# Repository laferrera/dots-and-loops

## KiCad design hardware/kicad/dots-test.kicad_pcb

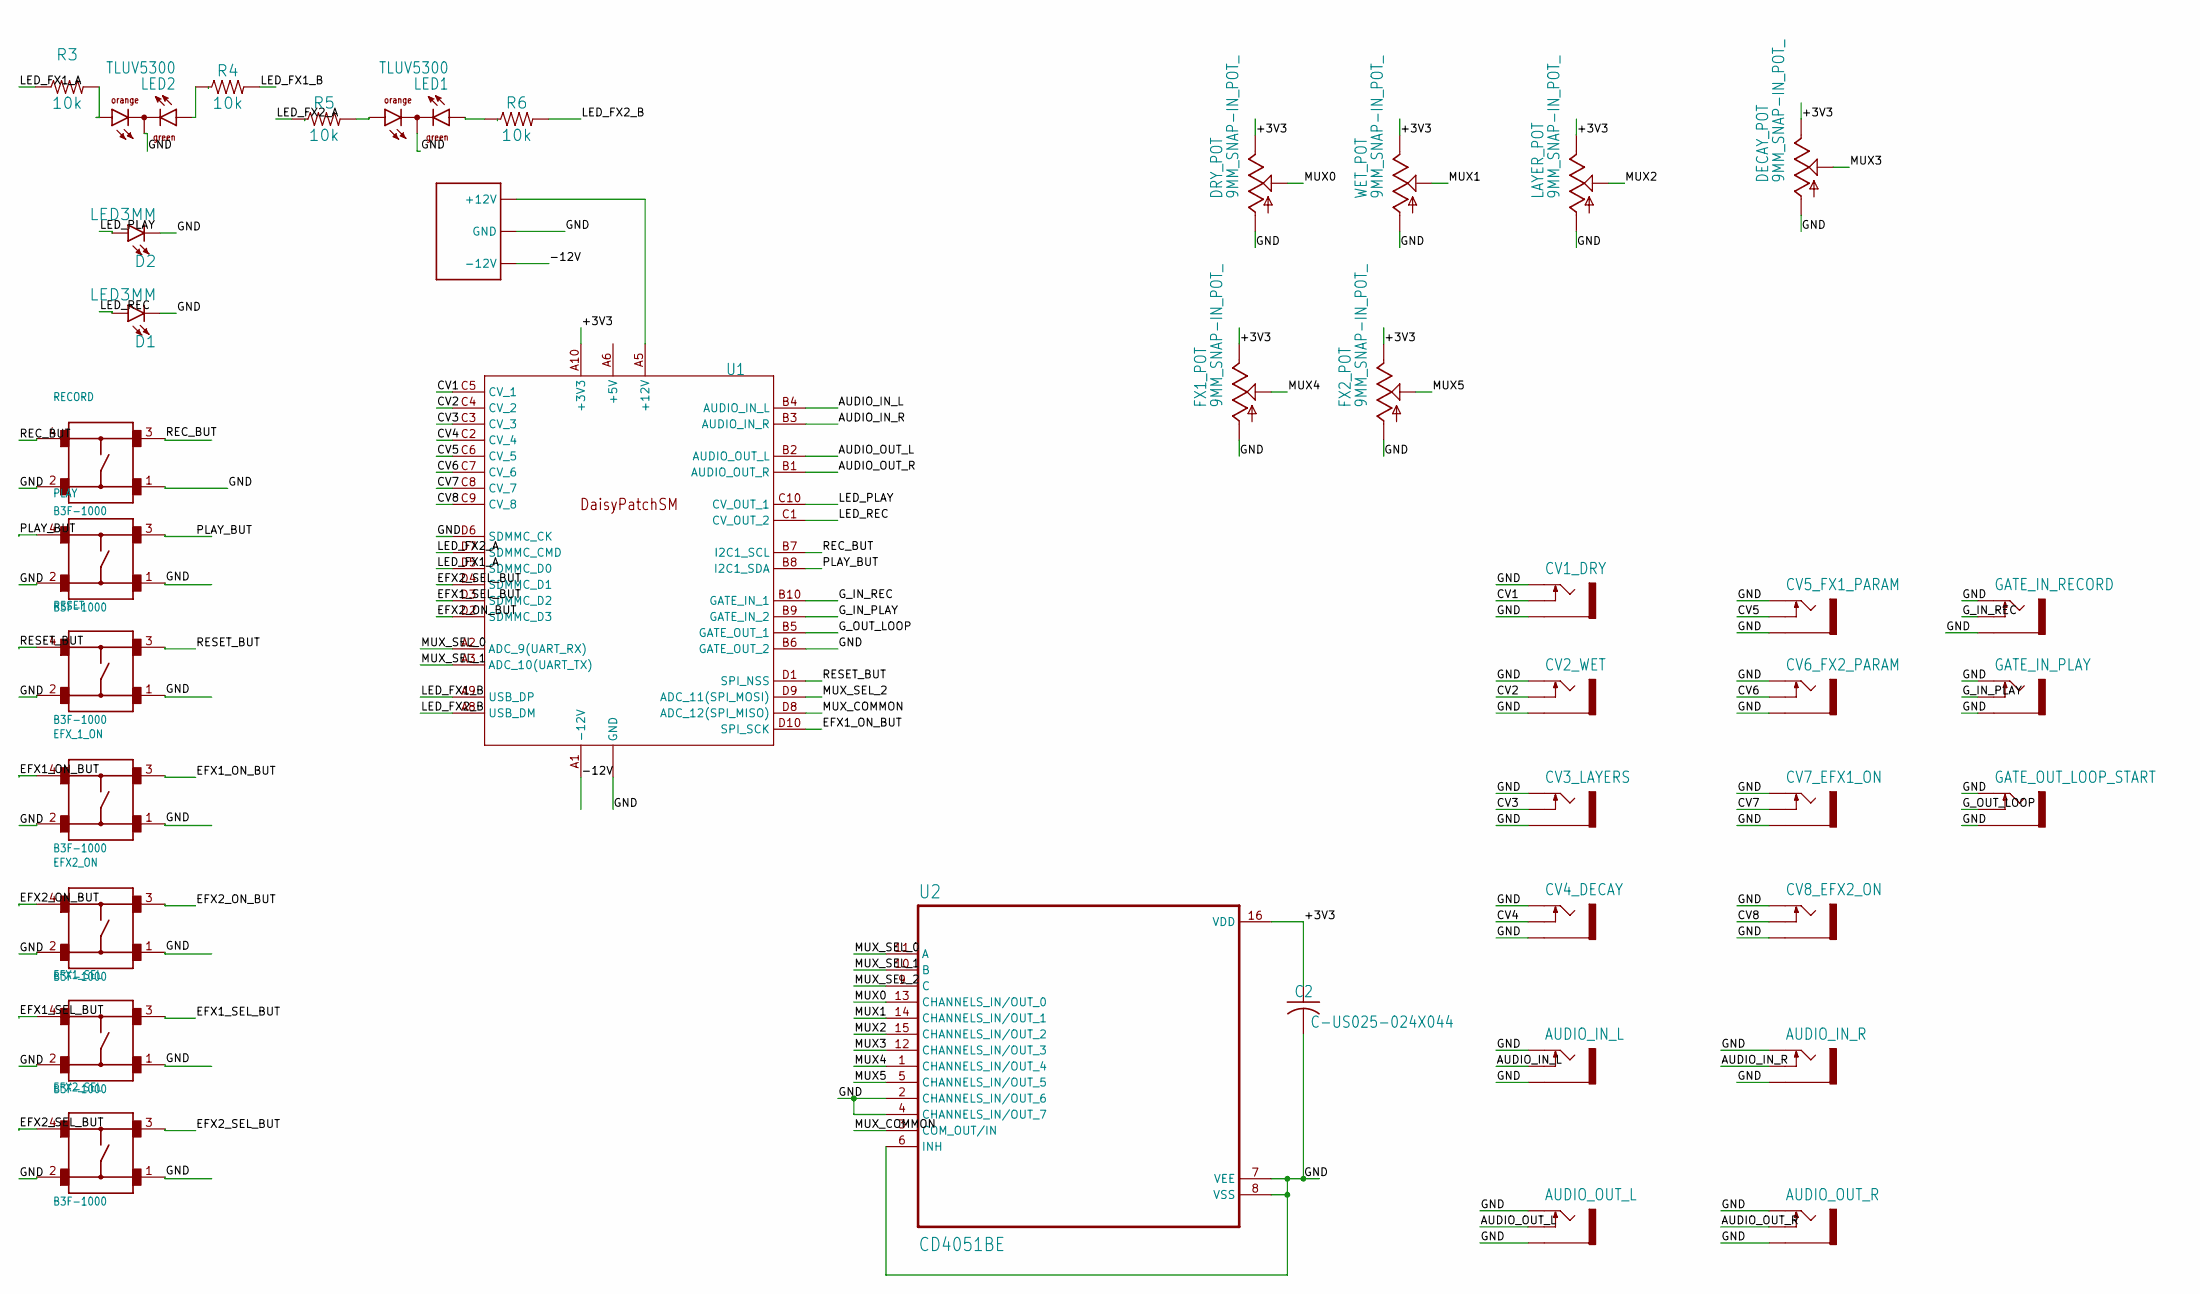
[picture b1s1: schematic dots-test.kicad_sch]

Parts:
AUDIO_IN_L: THONKICONNNEW; WQP-PJ301M-12_JACK
AUDIO_IN_R: THONKICONNNEW; WQP-PJ301M-12_JACK
AUDIO_OUT_L: THONKICONNNEW; WQP-PJ301M-12_JACK
AUDIO_OUT_R: THONKICONNNEW; WQP-PJ301M-12_JACK
C1: EURO_POWER_LOCKFAT-LOCK; EURO_PWR_HEADER_LOCK
C2: C-US025-024X044; C025-024X044
CV1_DRY, CV2_WET, CV3_LAYERS, CV4_DECAY, CV5_FX1_PARAM, CV6_FX2_PARAM, CV7_EFX1_ON, CV8_EFX2_ON: THONKICONNNEW; WQP-PJ301M-12_JACK
D1, D2: LED3MM; LED_3MM
DECAY_POT: 9MM_SNAP-IN_POT_; 9MM_SNAP-IN_POT
DRY_POT: 9MM_SNAP-IN_POT_; 9MM_SNAP-IN_POT
EFX1_SEL, EFX2_ON, EFX2_SEL: B3F-1000
EFX_1_ON: B3F-1000
FX1_POT, FX2_POT: 9MM_SNAP-IN_POT_; 9MM_SNAP-IN_POT
GATE_IN_PLAY: THONKICONNNEW; WQP-PJ301M-12_JACK
GATE_IN_RECORD: THONKICONNNEW; WQP-PJ301M-12_JACK
GATE_OUT_LOOP_START: THONKICONNNEW; WQP-PJ301M-12_JACK
LAYER_POT: 9MM_SNAP-IN_POT_; 9MM_SNAP-IN_POT
LED1, LED2: TLUV5300
PLAY: B3F-1000
R3, R4, R5, R6: 10k; AXIAL-0.3
RECORD: B3F-1000
RESET: B3F-1000
U1: ES_DAISY_PATCH_SMULTRA_LOCK; ES_DAISY_PATCH_SM_REV1_ULTRA_LOCK
U2: CD4051BE; DIP794W45P254L1969H508Q16
WET_POT: 9MM_SNAP-IN_POT_; 9MM_SNAP-IN_POT

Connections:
+3V3: C2.1, DECAY_POT.3 (E), DRY_POT.3 (E), FX1_POT.3 (E), FX2_POT.3 (E), LAYER_POT.3 (E), U1.A10 (+3V3), U2.16 (VDD), WET_POT.3 (E)
-12V: C1.NEG1 (-12V), C1.NEG2 (-12V), U1.A1 (-12V)
AUDIO_IN_L: AUDIO_IN_L.P$2_SWITCH (SWITCH), U1.B4 (AUDIO_IN_L)
AUDIO_IN_R: AUDIO_IN_R.P$2_SWITCH (SWITCH), U1.B3 (AUDIO_IN_R)
AUDIO_OUT_L: AUDIO_OUT_L.P$2_SWITCH (SWITCH), U1.B2 (AUDIO_OUT_L)
AUDIO_OUT_R: AUDIO_OUT_R.P$2_SWITCH (SWITCH), U1.B1 (AUDIO_OUT_R)
CV1: CV1_DRY.P$2_SWITCH (SWITCH), U1.C5 (CV_1)
CV2: CV2_WET.P$2_SWITCH (SWITCH), U1.C4 (CV_2)
CV3: CV3_LAYERS.P$2_SWITCH (SWITCH), U1.C3 (CV_3)
CV4: CV4_DECAY.P$2_SWITCH (SWITCH), U1.C2 (CV_4)
CV5: CV5_FX1_PARAM.P$2_SWITCH (SWITCH), U1.C6 (CV_5)
CV6: CV6_FX2_PARAM.P$2_SWITCH (SWITCH), U1.C7 (CV_6)
CV7: CV7_EFX1_ON.P$2_SWITCH (SWITCH), U1.C8 (CV_7)
CV8: CV8_EFX2_ON.P$2_SWITCH (SWITCH), U1.C9 (CV_8)
EFX1_ON_BUT: EFX_1_ON.3, EFX_1_ON.4, U1.D10 (SPI_SCK)
EFX1_SEL_BUT: EFX1_SEL.3, EFX1_SEL.4, U1.D3 (SDMMC_D2)
EFX2_ON_BUT: EFX2_ON.3, EFX2_ON.4, U1.D2 (SDMMC_D3)
EFX2_SEL_BUT: EFX2_SEL.3, EFX2_SEL.4, U1.D4 (SDMMC_D1)
GND: AUDIO_IN_L.P$1_TIP (TIP), AUDIO_IN_L.P$3_SLEEVE (SLEEVE), AUDIO_IN_R.P$1_TIP (TIP), AUDIO_IN_R.P$3_SLEEVE (SLEEVE), AUDIO_OUT_L.P$1_TIP (TIP), AUDIO_OUT_L.P$3_SLEEVE (SLEEVE), AUDIO_OUT_R.P$1_TIP (TIP), AUDIO_OUT_R.P$3_SLEEVE (SLEEVE), C1.GND1 (GND), C1.GND2 (GND), C1.GND3 (GND), C1.GND4 (GND), C1.GND5 (GND), C1.GND6 (GND), C2.2, CV1_DRY.P$1_TIP (TIP), CV1_DRY.P$3_SLEEVE (SLEEVE), CV2_WET.P$1_TIP (TIP), CV2_WET.P$3_SLEEVE (SLEEVE), CV3_LAYERS.P$1_TIP (TIP), CV3_LAYERS.P$3_SLEEVE (SLEEVE), CV4_DECAY.P$1_TIP (TIP), CV4_DECAY.P$3_SLEEVE (SLEEVE), CV5_FX1_PARAM.P$1_TIP (TIP), CV5_FX1_PARAM.P$3_SLEEVE (SLEEVE), CV6_FX2_PARAM.P$1_TIP (TIP), CV6_FX2_PARAM.P$3_SLEEVE (SLEEVE), CV7_EFX1_ON.P$1_TIP (TIP), CV7_EFX1_ON.P$3_SLEEVE (SLEEVE), CV8_EFX2_ON.P$1_TIP (TIP), CV8_EFX2_ON.P$3_SLEEVE (SLEEVE), D1.K (C), D2.K (C), DECAY_POT.1 (A), DRY_POT.1 (A), EFX1_SEL.1, EFX1_SEL.2, EFX2_ON.1, EFX2_ON.2, EFX2_SEL.1, EFX2_SEL.2, EFX_1_ON.1, EFX_1_ON.2, FX1_POT.1 (A), FX2_POT.1 (A), GATE_IN_PLAY.P$1_TIP (TIP), GATE_IN_PLAY.P$3_SLEEVE (SLEEVE), GATE_IN_RECORD.P$1_TIP (TIP), GATE_IN_RECORD.P$3_SLEEVE (SLEEVE), GATE_OUT_LOOP_START.P$1_TIP (TIP), GATE_OUT_LOOP_START.P$3_SLEEVE (SLEEVE), LAYER_POT.1 (A), LED1.CC, LED2.CC, PLAY.1, PLAY.2, RECORD.1, RECORD.2, RESET.1, RESET.2, U1.A4 (GND), U1.A7 (GND), U1.B6 (GATE_OUT_2), U1.D6 (SDMMC_CK), U2.2 (CHANNELS_IN/OUT_6), U2.4 (CHANNELS_IN/OUT_7), U2.6 (INH), U2.7 (VEE), U2.8 (VSS), WET_POT.1 (A)
G_IN_PLAY: GATE_IN_PLAY.P$2_SWITCH (SWITCH), U1.B9 (GATE_IN_2)
G_IN_REC: GATE_IN_RECORD.P$2_SWITCH (SWITCH), U1.B10 (GATE_IN_1)
G_OUT_LOOP: GATE_OUT_LOOP_START.P$2_SWITCH (SWITCH), U1.B5 (GATE_OUT_1)
LED_FX1_A: R3.P$1 (1), U1.D5 (SDMMC_D0)
LED_FX1_B: R4.P$2 (2), U1.A9 (USB_DP)
LED_FX2_A: R5.P$1 (1), U1.D7 (SDMMC_CMD)
LED_FX2_B: R6.P$2 (2), U1.A8 (USB_DM)
LED_PLAY: D2.A, U1.C10 (CV_OUT_1)
LED_REC: D1.A, U1.C1 (CV_OUT_2)
MUX0: DRY_POT.2 (S), U2.13 (CHANNELS_IN/OUT_0)
MUX1: U2.14 (CHANNELS_IN/OUT_1), WET_POT.2 (S)
MUX2: LAYER_POT.2 (S), U2.15 (CHANNELS_IN/OUT_2)
MUX3: DECAY_POT.2 (S), U2.12 (CHANNELS_IN/OUT_3)
MUX4: FX1_POT.2 (S), U2.1 (CHANNELS_IN/OUT_4)
MUX5: FX2_POT.2 (S), U2.5 (CHANNELS_IN/OUT_5)
MUX_COMMON: U1.D8 (ADC_12(SPI_MISO)), U2.3 (COM_OUT/IN)
MUX_SEL_0: U1.A2 (ADC_9(UART_RX)), U2.11 (A)
MUX_SEL_1: U1.A3 (ADC_10(UART_TX)), U2.10 (B)
MUX_SEL_2: U1.D9 (ADC_11(SPI_MOSI)), U2.9 (C)
unnamed: C1.POS1 (+12V), C1.POS2 (+12V), U1.A5 (+12V)
unnamed: LED2.AO, R3.P$2 (2)
unnamed: LED2.AG, R4.P$1 (1)
unnamed: LED1.AO, R5.P$2 (2)
unnamed: LED1.AG, R6.P$1 (1)
PLAY_BUT: PLAY.3, PLAY.4, U1.B8 (I2C1_SDA)
REC_BUT: RECORD.3, RECORD.4, U1.B7 (I2C1_SCL)
RESET_BUT: RESET.3, RESET.4, U1.D1 (SPI_NSS)

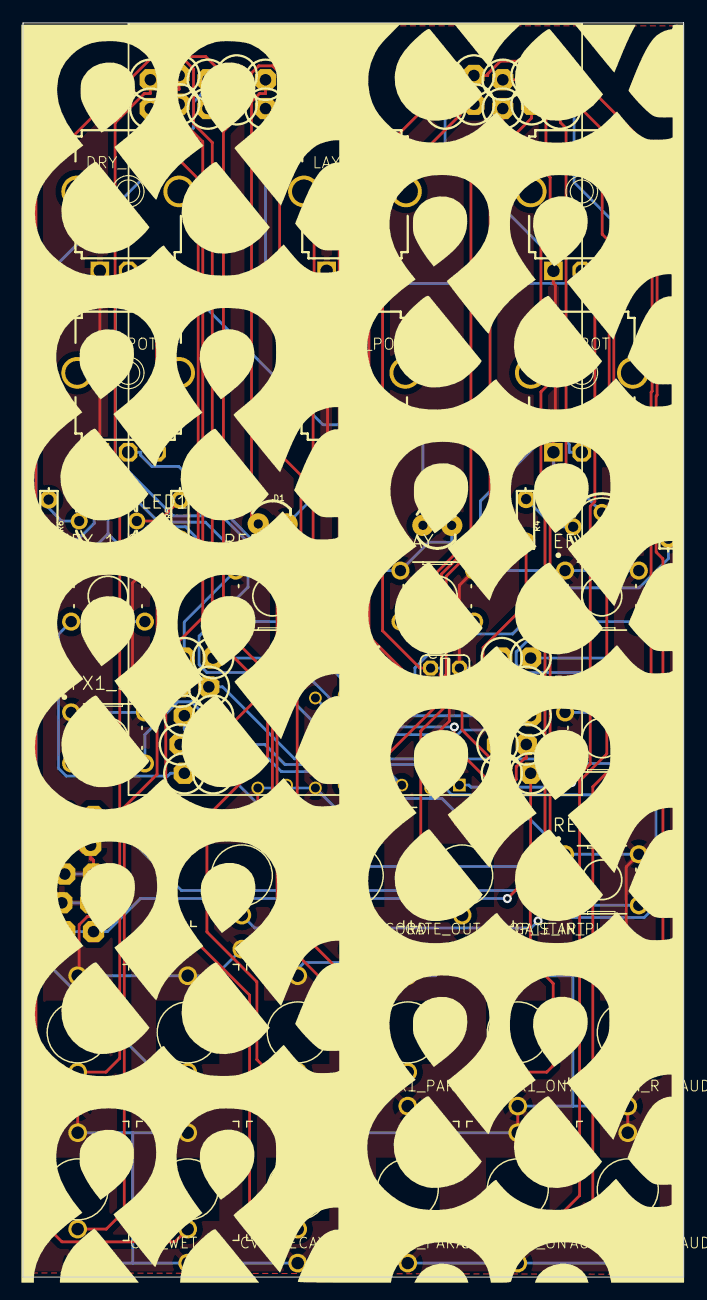
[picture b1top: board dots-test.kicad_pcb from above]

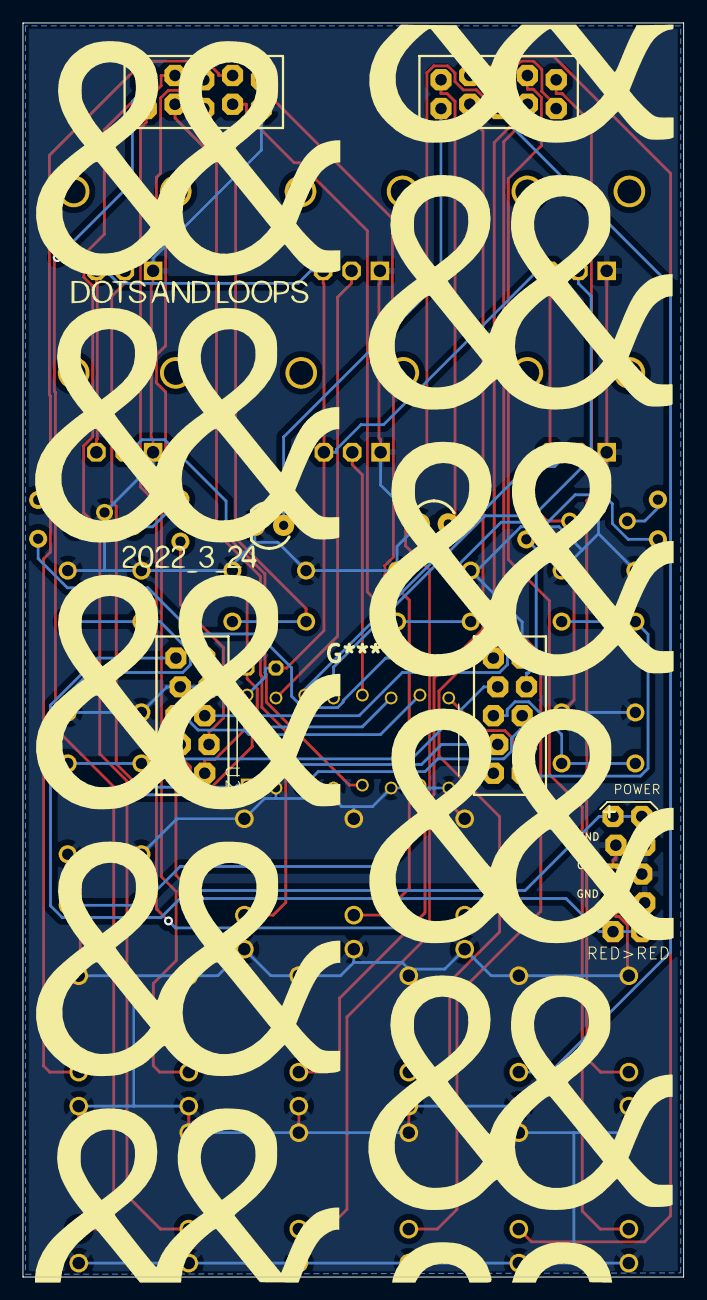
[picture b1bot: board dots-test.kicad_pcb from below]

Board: 2 copper layers, 58.3 x 110.6 mm, 40 parts (2 on the bottom side), 46 nets.
